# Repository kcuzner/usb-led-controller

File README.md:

# USB-attached LED controller

This is an LED controller for the lights that came with my In-Win A1 Mini-ITX Tower. It came with a simple 12V RGB LED
strip, rather than the now-standard WS2812 addressable LED strips that are so common in today's PCs.

I made one of these **ages** ago for my first self-built computer using all through-hole components and an AVR
microcontroller. It eventually broke after I shorted one of the MOSFETs out on my case when banging around in there
while it was turned on.

This one is a refresh of that idea, with a few additions I've picked up after another decade of tinkering:

 - STM32L042 microcontroller with crystal-less USB capability.
 - Outputs for 12V RGB and 5V WS2812.
 - 2.5" HDD screw pattern for mounting.
 - No secondary side or through-hole components.
 - Driverless HID device implementation.
 - Linux control daemon.
 - Windows control service.

## 2021 Part Shortage notes

 - STM32 can be swapped out for:
   - Silabs EFM32HG family
    - EFM32HG308 in the 24-QFN package has enough timers and UARTs to support the application
   - Microchip AT SAM L22 family
 - FETs are jellybean
 - Regulator might be integrated into uC
 - Level translator has no direct replacement
   - Do I really need the tristate version? Why?
   - The SN74LVC1T04 (inverter, non-tristate) seems available. Could I run this inverted?

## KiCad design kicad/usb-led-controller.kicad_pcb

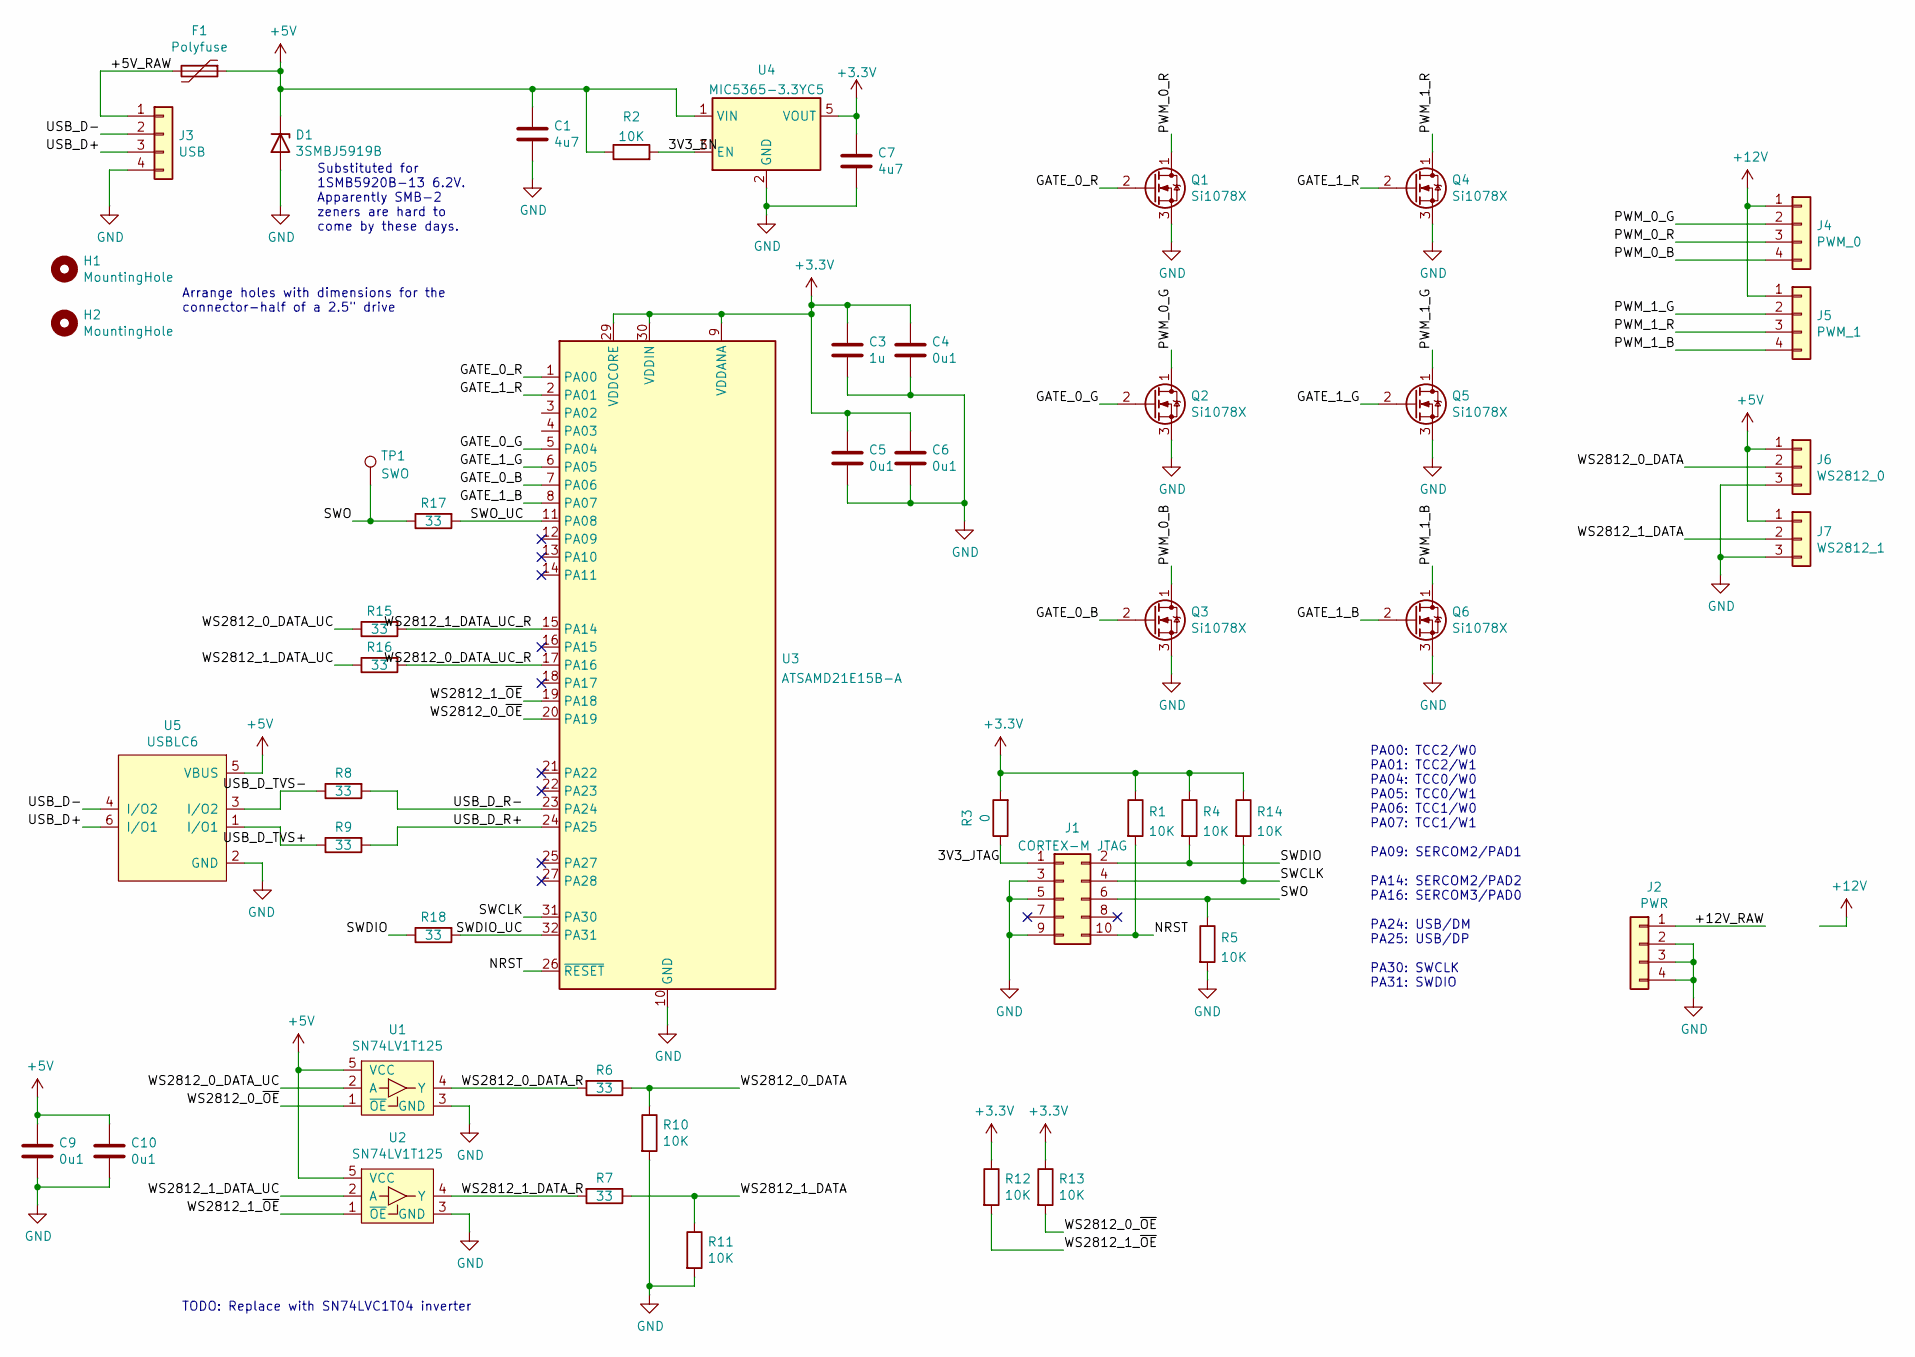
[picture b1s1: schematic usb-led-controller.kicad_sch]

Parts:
C1, C7: 4u7; C_0603_1608Metric; Part Number 1276-1044-2-ND
C3: 1u; C_0603_1608Metric; Part Number 1276-1102-2-ND
C4, C5, C6, C9, C10: 0u1; C_0402_1005Metric; Part Number 1276-1043-2-ND
D1: 3SMBJ5919B; D_SMB; Part Number 3SMBJ5919B-TPMSTR-ND
F1: Polyfuse; R_1812_4532Metric; Part Number 507-1762-2-ND
H1, H2: MountingHole; MountingHole_3.2mm_M3
J1: CORTEX-M JTAG; CORTEX-SWD-CONNECTOR
J2: PWR; M20-88904; Part Number 952-3233-ND
J3: USB; M20-88904; Part Number 952-3233-ND
J4: PWM_0; M20-88904; Part Number 952-3233-ND
J5: PWM_1; M20-88904; Part Number 952-3233-ND
J6: WS2812_0; M20-88903; Part Number 952-3232-ND
J7: WS2812_1; M20-88903; Part Number 952-3232-ND
Q1, Q2, Q3, Q4, Q5, Q6: Si1078X; SC-89
R1, R2, R4, R5, R14: 10K; R_0402_1005Metric
R3: 0; R_0402_1005Metric
R6, R7, R8, R9, R15, R16, R17, R18: 33; R_0402_1005Metric; Part Number CR0402-JW-330GLFTR-ND
R10, R11, R12, R13: 10K; R_0402_1005Metric; Part Number CR0402-JW-103GLFTR-ND
TP1: SWO; TestPoint_Pad_D1.5mm
U1, U2: SN74LV1T125; SOT-353_SC-70-5; Part Number 296-37173-2-ND
U3: ATSAMD21E15B-A; TQFP-32_7x7mm_P0.8mm
U4: MIC5365-3.3YC5; SOT-353_SC-70-5
U5: USBLC6; SOT-666; Part Number 497-5026-2-ND

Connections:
+3V3: C3.1, C4.1, C5.1, C6.1, C7.1, R1.1, R3.2, R4.1, R12.1, R13.1, R14.1, U3.9 (VDDANA), U3.29 (VDDCORE), U3.30 (VDDIN), U4.5 (VOUT)
+5V: C1.1, C9.1, C10.1, D1.1 (K), F1.1, J6.1, J7.1, R2.1, U1.5 (VCC), U2.5 (VCC), U4.1 (VIN), U5.5 (VBUS)
+12V: J4.1, J5.1; also elsewhere on the board
/3V3_EN: R2.2, U4.3 (EN)
/3V3_JTAG: J1.1, R3.1
/+5V_RAW: F1.2, J3.1
/+12V_RAW: J2.1; also elsewhere on the board
/GATE_0_B: Q3.2 (G), U3.7 (PA06)
/GATE_0_G: Q2.2 (G), U3.5 (PA04)
/GATE_0_R: Q1.2 (G), U3.1 (PA00)
/GATE_1_B: Q6.2 (G), U3.8 (PA07)
/GATE_1_G: Q5.2 (G), U3.6 (PA05)
/GATE_1_R: Q4.2 (G), U3.2 (PA01)
/NRST: J1.10, R1.2, U3.26 (~RESET)
/PWM_0_B: J4.4, Q3.1 (D)
/PWM_0_G: J4.2, Q2.1 (D)
/PWM_0_R: J4.3, Q1.1 (D)
/PWM_1_B: J5.4, Q6.1 (D)
/PWM_1_G: J5.2, Q5.1 (D)
/PWM_1_R: J5.3, Q4.1 (D)
/SWCLK: J1.4, R14.2, U3.31 (PA30)
/SWDIO: J1.2, R4.2, R18.1
/SWDIO_UC: R18.2, U3.32 (PA31)
/SWO: J1.6, R5.1, R17.1, TP1.1
/SWO_UC: R17.2, U3.11 (PA08)
/USB_D+: J3.3, U5.6 (I/O1)
/USB_D-: J3.2, U5.4 (I/O2)
/USB_D_R+: R9.2, U3.24 (PA25)
/USB_D_R-: R8.2, U3.23 (PA24)
/USB_D_TVS+: R9.1, U5.1 (I/O1)
/USB_D_TVS-: R8.1, U5.3 (I/O2)
/WS2812_0_DATA: J6.2, R6.1, R10.1
/WS2812_0_DATA_R: R6.2, U1.4 (Y)
/WS2812_0_DATA_UC: R15.1, U1.2 (A)
/WS2812_0_DATA_UC_R: R16.2, U3.17 (PA16)
/WS2812_0_~OE: R13.2, U1.1 (~OE), U3.20 (PA19)
/WS2812_1_DATA: J7.2, R7.1, R11.1
/WS2812_1_DATA_R: R7.2, U2.4 (Y)
/WS2812_1_DATA_UC: R16.1, U2.2 (A)
/WS2812_1_DATA_UC_R: R15.2, U3.15 (PA14)
/WS2812_1_~OE: R12.2, U2.1 (~OE), U3.19 (PA18)
GND: C1.2, C3.2, C4.2, C5.2, C6.2, C7.2, C9.2, C10.2, D1.2 (A), J1.3, J1.5, J1.9, J2.2, J2.3, J2.4, J3.4, J6.3, J7.3, Q1.3 (S), Q2.3 (S), Q3.3 (S), Q4.3 (S), Q5.3 (S), Q6.3 (S), R5.2, R10.2, R11.2, U1.3 (GND), U2.3 (GND), U3.10 (GND), U3.28 (GND), U4.2 (GND), U5.2 (GND)

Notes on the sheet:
TODO: Replace with SN74LVC1T04 inverter
PA00: TCC2/W0 PA01: TCC2/W1 PA04: TCC0/W0 PA05: TCC0/W1 PA06: TCC1/W0 PA07: TCC1/W1 PA09: SERCOM2/PAD1 PA14: SERCOM2/PAD2 PA16: SERCOM3/PAD0 PA24: USB/DM PA25: USB/DP PA30: SWCLK PA31: SWDIO
Arrange holes with dimensions for the connector-half of a 2.5" drive
Substituted for 1SMB5920B-13 6.2V. Apparently SMB-2 zeners are hard to come by these days.

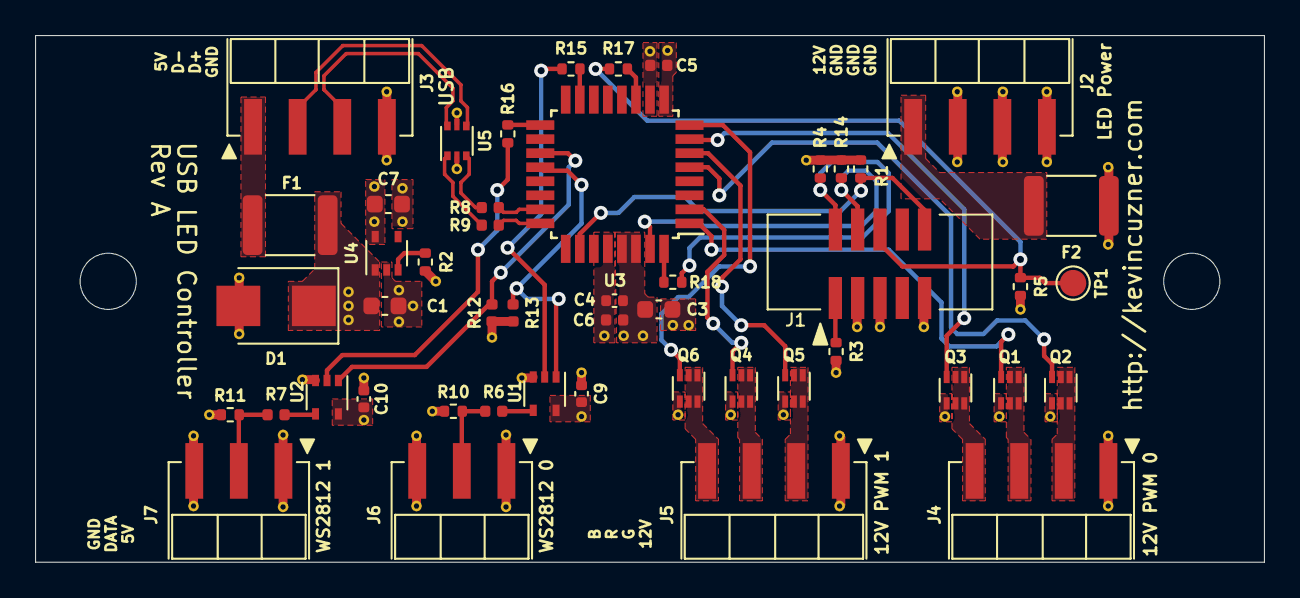
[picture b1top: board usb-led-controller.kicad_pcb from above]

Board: 4 copper layers, 70.0 x 30.0 mm, 50 parts (0 on the bottom side), 42 nets.

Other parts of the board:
F2: Polyfuse; R_1812_4532Metric

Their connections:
+12V: F2.1; also elsewhere on the board
/+12V_RAW: F2.2; also elsewhere on the board

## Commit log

2020-11-23 Adding a couple parts to the schematic
2020-11-26 Adding initial schematic
    The PWM outputs are driven with the microcontroller PWM. The WS2812
    outputs are driven from UARTS with DMA capability.
2020-11-27 Determined board form factor and placed connectors
2020-11-27 Configuring 4-layer board stackup with netclasses
2020-11-27 Changing microcontroller and redoing WS2812 control
    The QFN package required VIPPO to be easily soldered. I could
    probably have done it without plating-over, but it still requires the
    heat gun and it is currently broken.
    The family was downgraded to an ST32F042, which is a little clunkier
    than the STM32L052 family. It also doesn't have very accessible UARTs
    when USB is being used, so I swapped out the level shifters to tri-state
2020-11-27 Adding pulldowns on WS2812 outputs
2020-11-28 Added polyfuses and reduced board size
    This is much more reasonable. No need to take up all that space.
2020-11-28 Added power planes to 3rd layer
2020-11-28 Added power planes on top layer and a few traces
2020-11-28 Cmopleted initial routing
2020-11-28 Cleaning up silkscreen
2020-11-28 Added some pullups
2020-12-29 Adding text to silkscreen
2020-12-29 Minor silkscreen cleanup, saving with new kicad
2021-09-06 Updated part numbers on schematic for building
    This doesn't belong on this branch..
2021-09-06 Noting several possible part substitutions for shortages
2021-09-06 Updating schematic to use an EFM32HG microcontroller
2021-09-06 Placed new microcontroller and rearranged capacitors
2021-09-06 Completed routing around the new microcontroller
2021-09-06 Fixed silkscreen of new components
2021-09-07 Fixed pad connection on ground layer to be solid
2022-02-08 Upgrading to Kicad 6
2022-02-20 Changing microcontroller to ATSAMD21E15B
2022-08-13 Changing programmer header to standard ARM Cortex one
2022-08-14 Changing FET selection, fixing stackup, adding CYA resistors
2022-08-14 Gerber out Rev A
